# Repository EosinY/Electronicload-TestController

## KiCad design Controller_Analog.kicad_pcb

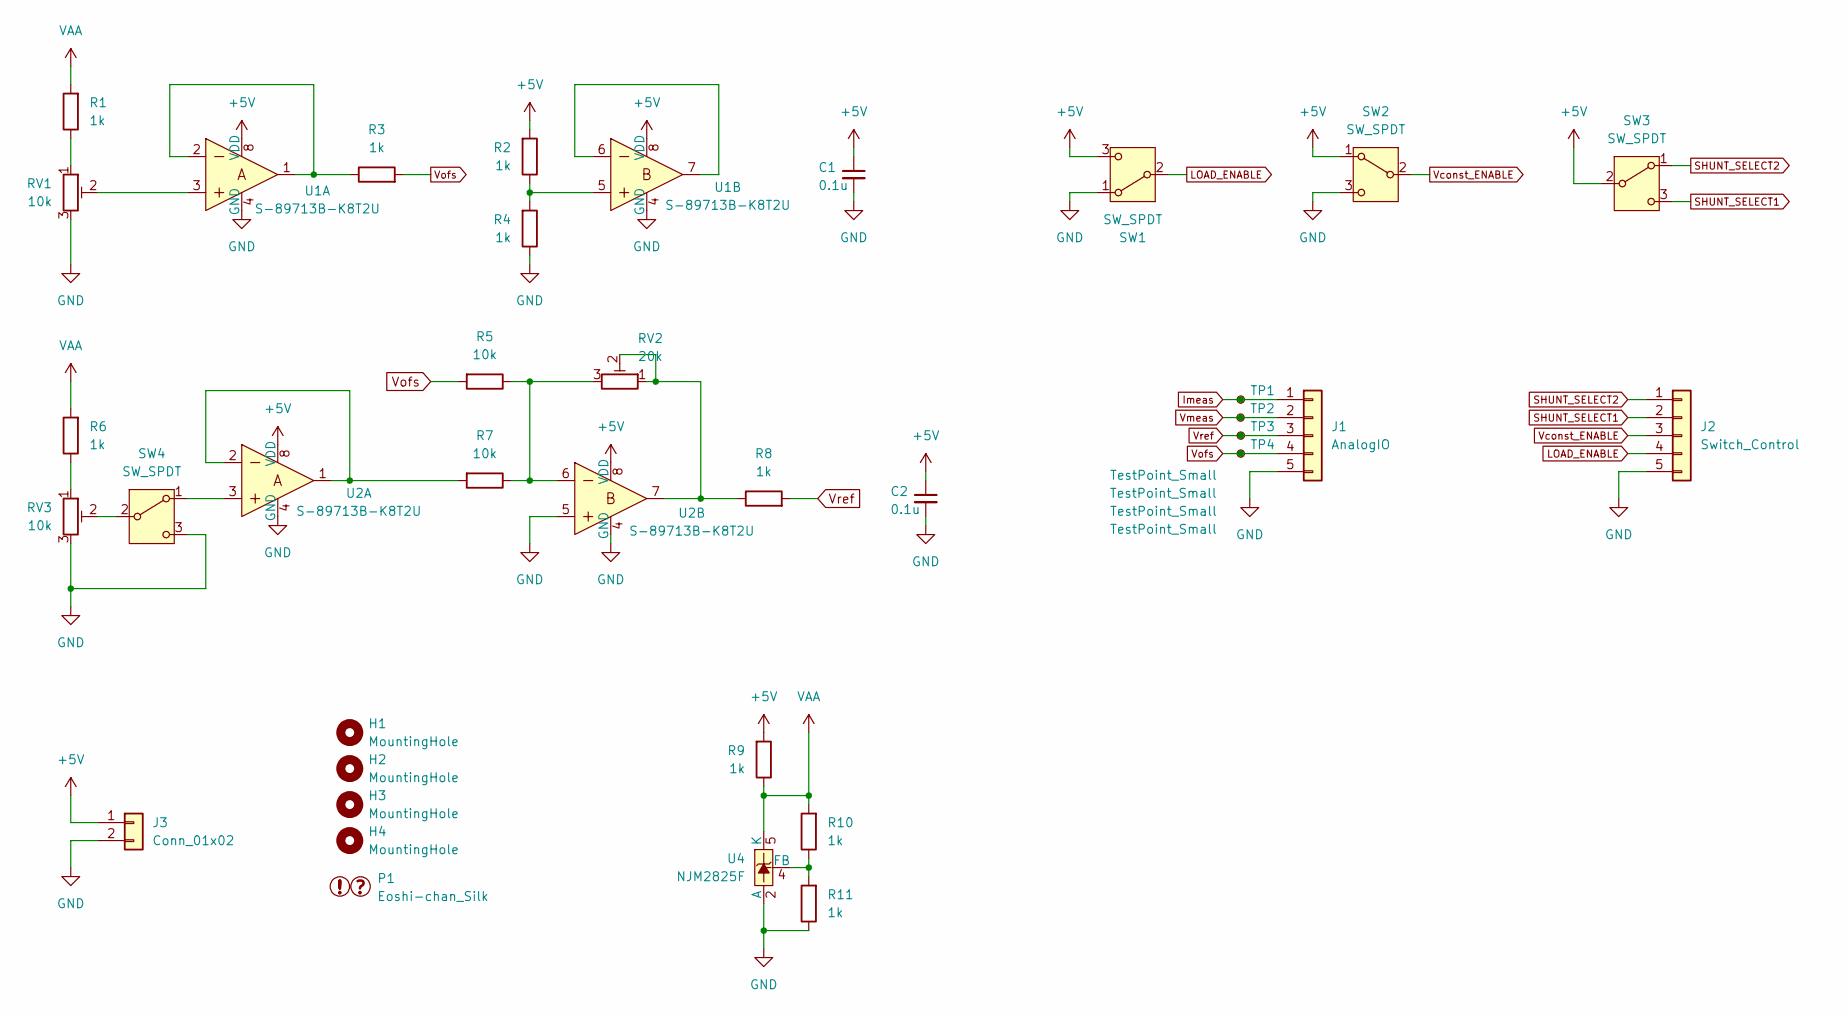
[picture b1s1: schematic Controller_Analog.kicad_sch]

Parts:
C1, C2: 0.1u; C_0603_1608Metric
H1, H2, H3, H4: MountingHole; MountingHole_3.2mm_M3
J1: AnalogIO; JST_XH_B5B-XH-A_1x05_P2.50mm_Vertical
J2: Switch_Control; JST_XH_B5B-XH-A_1x05_P2.50mm_Vertical
J3: Conn_01x02; JST_XH_B2B-XH-A_1x02_P2.50mm_Vertical
P1: Eoshi-chan_Silk; Eoshi-chan-v2_10x10
R1, R2, R3, R4, R6, R8: 1k; R_0603_1608Metric
R5, R7: 10k; R_Axial_DIN0207_L6.3mm_D2.5mm_P10.16mm_Horizontal
R9, R10, R11: 1k; R_Axial_DIN0207_L6.3mm_D2.5mm_P10.16mm_Horizontal
RV1: 10k; Potentiometer_Vishay_T73YP_Vertical
RV2: 20k; Potentiometer_Vishay_T73YP_Vertical
RV3: 10k; Potentiometer_Alps_RK09K_Single_Vertical
SW1, SW4: SW_SPDT; 2MS1-T1-B4-M2-Q-E
SW2, SW3: SW_SPDT; SS-12D00G3
TP1, TP2, TP3, TP4: TestPoint_Small; TestPoint_THTPad_D2.0mm_Drill1.0mm
U1, U2: S-89713B-K8T2U; MSOP-8_3x3mm_P0.65mm
U4: NJM2825F; SOT-23-5

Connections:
+5V: C1.1, C2.1, J3.1, R2.2, R9.2, SW1.3 (C), SW2.1 (A), SW3.2 (B), U1.8 (VDD), U2.8 (VDD)
GND: C1.2, C2.2, J1.5, J2.5, J3.2, R4.1, R11.1, RV1.3, RV3.3, SW1.1 (A), SW2.3 (C), SW4.3 (C), U1.4 (GND), U2.4 (GND), U2.5, U4.2 (A)
Imeas: J1.1, TP1.1
LOAD_ENABLE: J2.4, SW1.2 (B)
unnamed: R1.1, RV1.1
unnamed: R2.1, R4.2, U1.5
unnamed: R3.1, U1.1, U1.2
unnamed: R5.1, R7.1, RV2.3, U2.6
unnamed: R6.1, RV3.1
unnamed: R7.2, U2.1, U2.2
unnamed: R8.1, RV2.1, RV2.2, U2.7
unnamed: RV1.2, U1.3
unnamed: SW4.1 (A), U2.3
unnamed: RV3.2, SW4.2 (B)
unnamed: U1.6, U1.7
unnamed: R10.1, R11.2, U4.4 (FB)
SHUNT_SELECT1: J2.2, SW3.3 (C)
SHUNT_SELECT2: J2.1, SW3.1 (A)
VAA: R1.2, R6.2, R9.1, R10.2, U4.5 (K)
Vconst_ENABLE: J2.3, SW2.2 (B)
Vmeas: J1.2, TP2.1
Vofs: J1.4, R3.2, R5.2, TP4.1
Vref: J1.3, R8.2, TP3.1

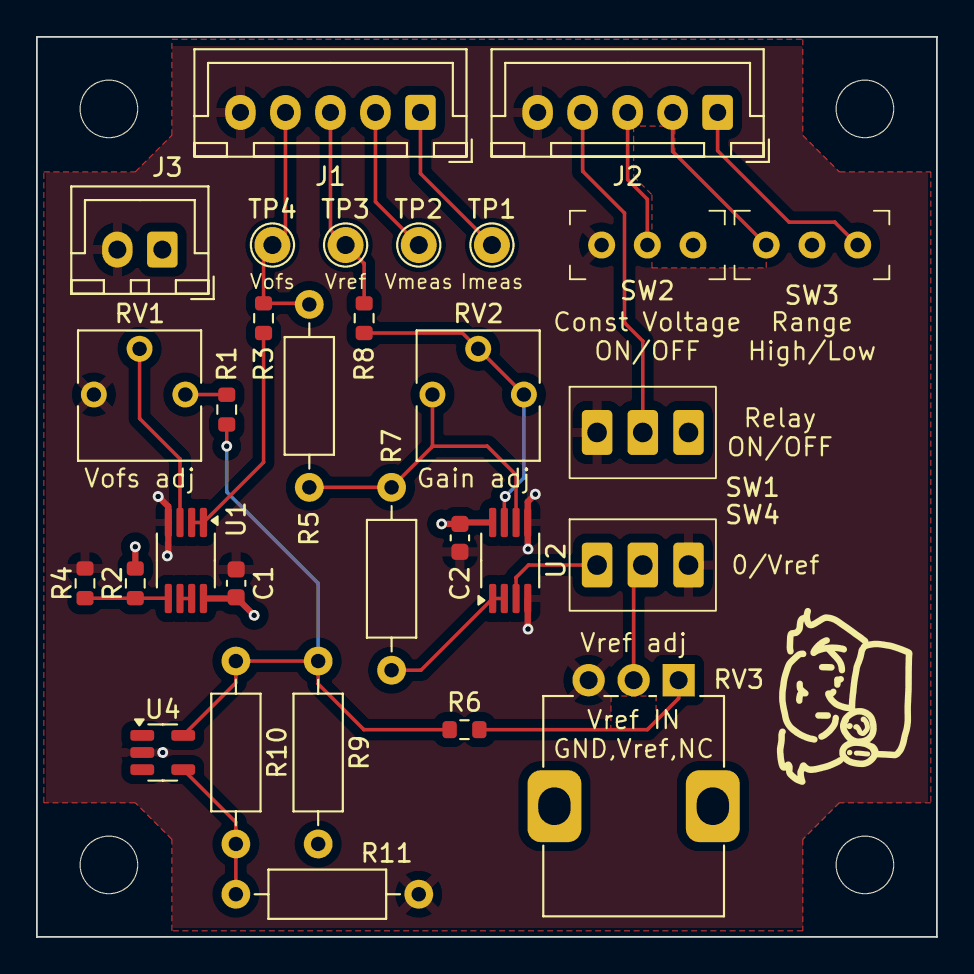
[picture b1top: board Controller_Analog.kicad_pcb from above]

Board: 4 copper layers, 50.0 x 50.0 mm, 35 parts (0 on the bottom side), 23 nets.

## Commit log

2025-05-07 first
2025-05-07 add gitignore
2025-05-29 add Universal Board version
2025-05-31 wired components
